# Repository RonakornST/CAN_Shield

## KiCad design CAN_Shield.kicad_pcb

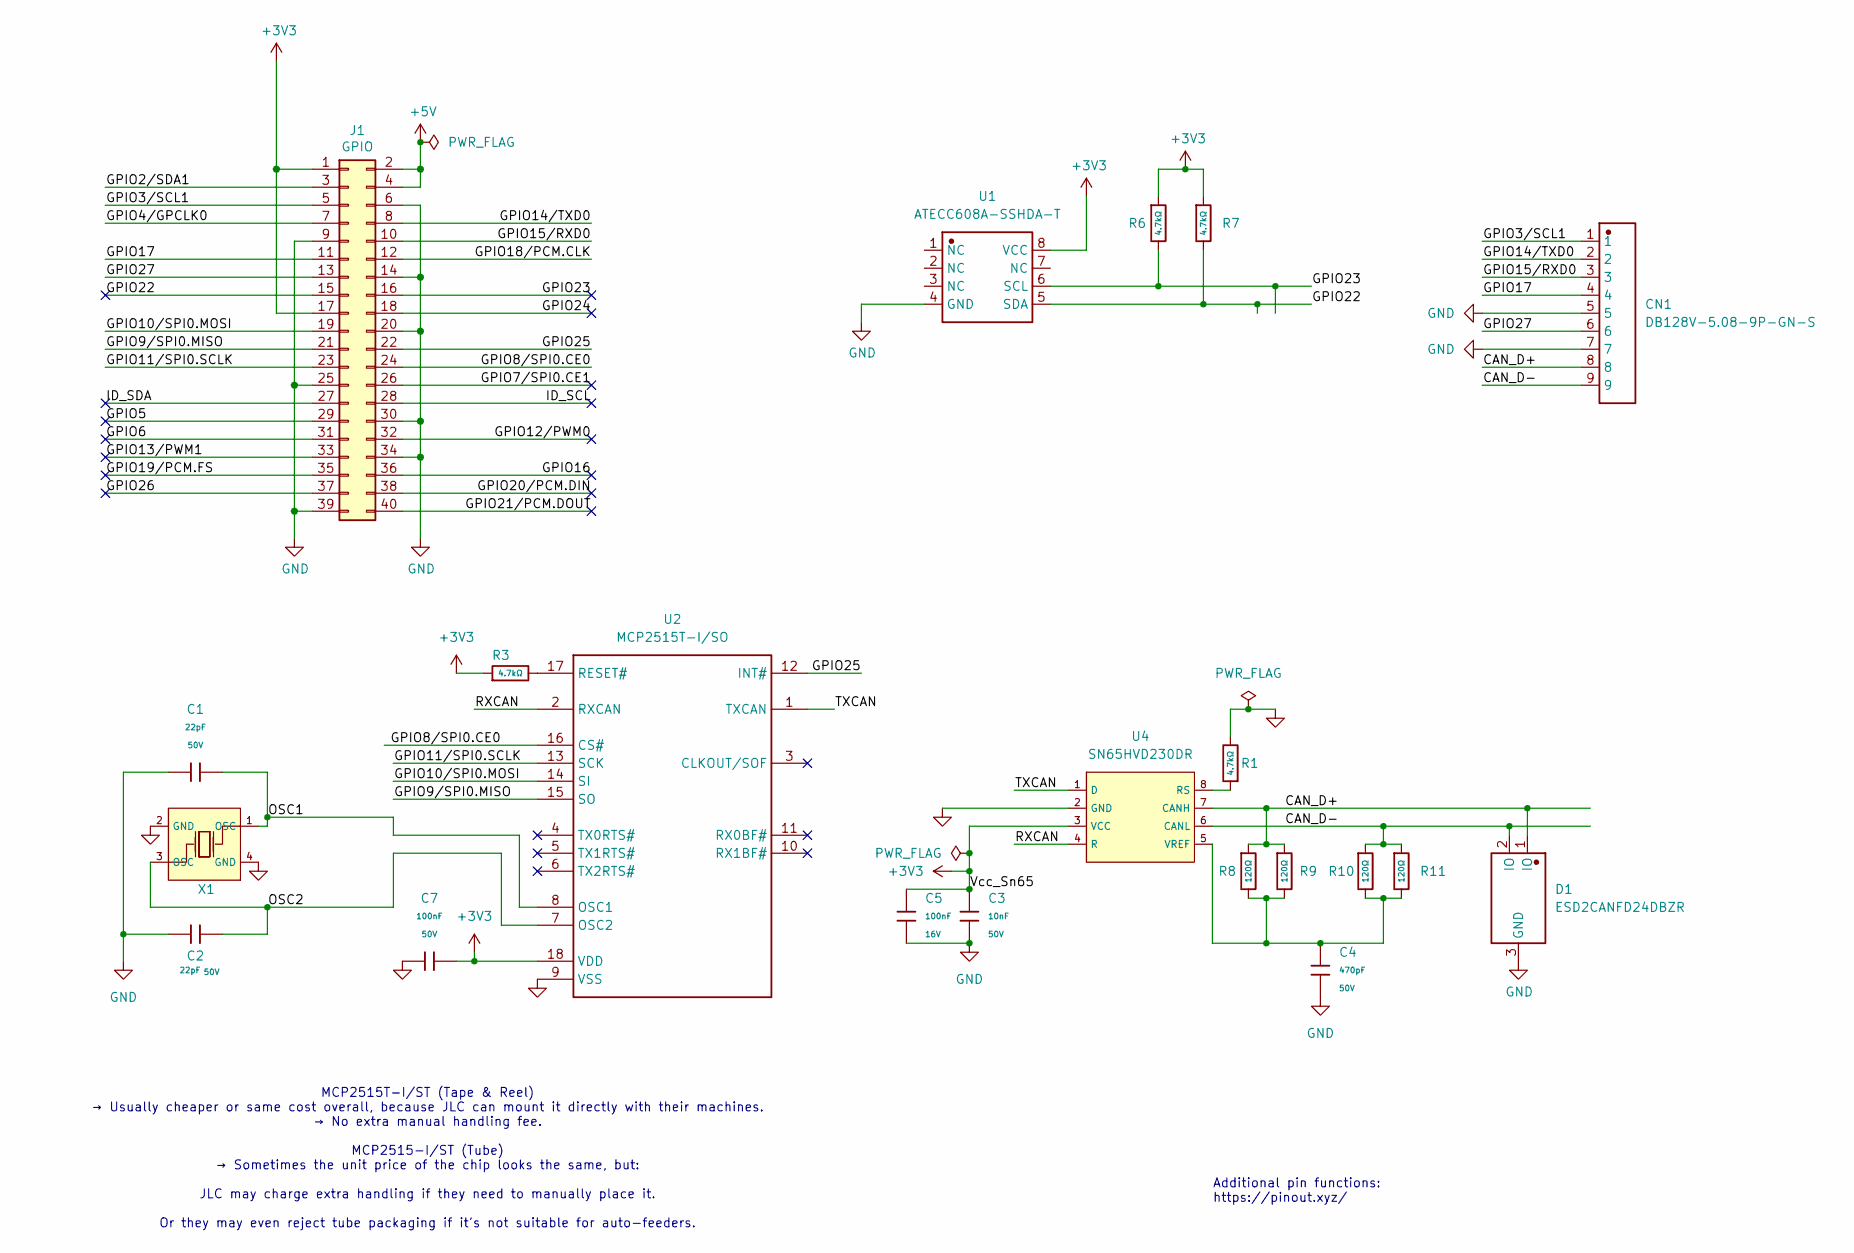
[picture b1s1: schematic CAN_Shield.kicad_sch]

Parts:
C1, C2: 22pF; C_0402; Voltage Rated 50V; Tolerance ±5%; Part 0402CG220J500NT; LCSC C1555
C3: 10nF; C_0402; Voltage Rated 50V; Tolerance ±10%; Part CL05B103KB5NNNC; LCSC C15195
C4: 470pF; C_0402; Voltage Rated 50V; Tolerance ±10%; Part 0402B471K500NT; LCSC C1537
C5: 100nF; C_0402; Voltage Rated 16V; Tolerance ±10%; Part CL05B104KO5NNNC; LCSC C1525
C7: 100nF; C_0603; Voltage Rated 50V; Tolerance ±10%; Part CC0603KRX7R9BB104; LCSC C14663
CN1: DB128V-5.08-9P-GN-S; CONN-TH_9P-P5.08_DIBO_DB128V-5.08-9P-GN-S; Manufacturer Part DB128V-5.08-9P-GN-S
D1: ESD2CANFD24DBZR; TI ESD2CANFD24DBZR; Manufacturer Part ESD2CANFD24DBZR
J1: GPIO; PinSocket_2x20_P2.54mm_Vertical
R1, R3, R6, R7: 4.7kΩ; R_0402; Overload Voltage (Max) 50V; Tolerance ±1%; Part 0402WGF4701TCE; LCSC C25900
R8, R9, R10, R11: 120Ω; R_0402; Overload Voltage (Max) 50V; Tolerance ±1%; Part 0402WGF1200TCE; LCSC C25079
U1: ATECC608A-SSHDA-T; MICROCHIP ATECC608A-SSHDA-T; Manufacturer Part ATECC608A-SSHDA-T
U2: MCP2515T-I/SO; MCP2515T-IST_SOIC-18_L11.6-W7.5-P1.27-LS10.3-BL; Manufacturer Part MCP2515T-I/SO
U4: SN65HVD230DR; SOIC-8_L4.9-W3.9-P1.27-LS6.0-BL; Supply Voltage 3V~3.6V; Part SN65HVD230DR; LCSC C12084
X1: X322516MLB4SI; OSC-SMD_4P-L3.2-W2.5-BL; Frequency Tolerance ±10ppm; Part X322516MLB4SI; LCSC C13738

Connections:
+3V3: C3.1, C5.1, C7.2, J1.1, J1.17, R3.1, R6.1, R7.1, U1.8 (VCC), U2.18 (VDD), U4.3 (VCC)
+5V: J1.2, J1.4
/CAN_D+: CN1.8, D1.1 (IO), R8.1, R9.1, U4.7 (CANH)
/CAN_D-: CN1.9, D1.2 (IO), R10.1, R11.1, U4.6 (CANL)
/GPIO2/SDA1: J1.3
/GPIO3/SCL1: CN1.1, J1.5
/GPIO4/GPCLK0: J1.7
/GPIO5: J1.29
/GPIO6: J1.31
/GPIO7/SPI0.CE1: J1.26
/GPIO8/SPI0.CE0: J1.24, U2.16 (CS#)
/GPIO9/SPI0.MISO: J1.21, U2.15 (SO)
/GPIO10/SPI0.MOSI: J1.19, U2.14 (SI)
/GPIO11/SPI0.SCLK: J1.23, U2.13 (SCK)
/GPIO12/PWM0: J1.32
/GPIO13/PWM1: J1.33
/GPIO14/TXD0: CN1.2, J1.8
/GPIO15/RXD0: CN1.3, J1.10
/GPIO16: J1.36
/GPIO17: CN1.4, J1.11
/GPIO18/PCM.CLK: J1.12
/GPIO19/PCM.FS: J1.35
/GPIO20/PCM.DIN: J1.38
/GPIO21/PCM.DOUT: J1.40
/GPIO22: J1.15, R7.2, U1.5 (SDA)
/GPIO23: J1.16, R6.2, U1.6 (SCL)
/GPIO24: J1.18
/GPIO25: J1.22, U2.12 (INT#)
/GPIO26: J1.37
/GPIO27: CN1.6, J1.13
/ID_SCL: J1.28
/ID_SDA: J1.27
/OSC1: C1.2, U2.8 (OSC1), X1.1 (OSC)
/OSC2: C2.2, U2.7 (OSC2), X1.3 (OSC)
/RXCAN: U2.2 (RXCAN), U4.4 (R)
/TXCAN: U2.1 (TXCAN), U4.1 (D)
GND: C1.1, C2.1, C3.2, C4.2, C5.2, C7.1, CN1.5, CN1.7, D1.3 (GND), J1.6, J1.9, J1.14, J1.20, J1.25, J1.30, J1.34, J1.39, R1.2, U1.4 (GND), U2.9 (VSS), U4.2 (GND), X1.2 (GND), X1.4 (GND)
unnamed: R3.2, U2.17 (RESET#)
unnamed: R1.1, U4.8 (RS)
unnamed: C4.1, R8.2, R9.2, R10.2, R11.2, U4.5 (VREF)

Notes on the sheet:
Additional pin functions: https://pinout.xyz/
MCP2515T-I/ST (Tape & Reel) → Usually cheaper or same cost overall, because JLC can mount it directly with their machines. → No extra manual handling fee. MCP2515-I/ST (Tube) → Sometimes the unit price of the chip looks the same, but: JLC may charge extra handling if they need to manually place it.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

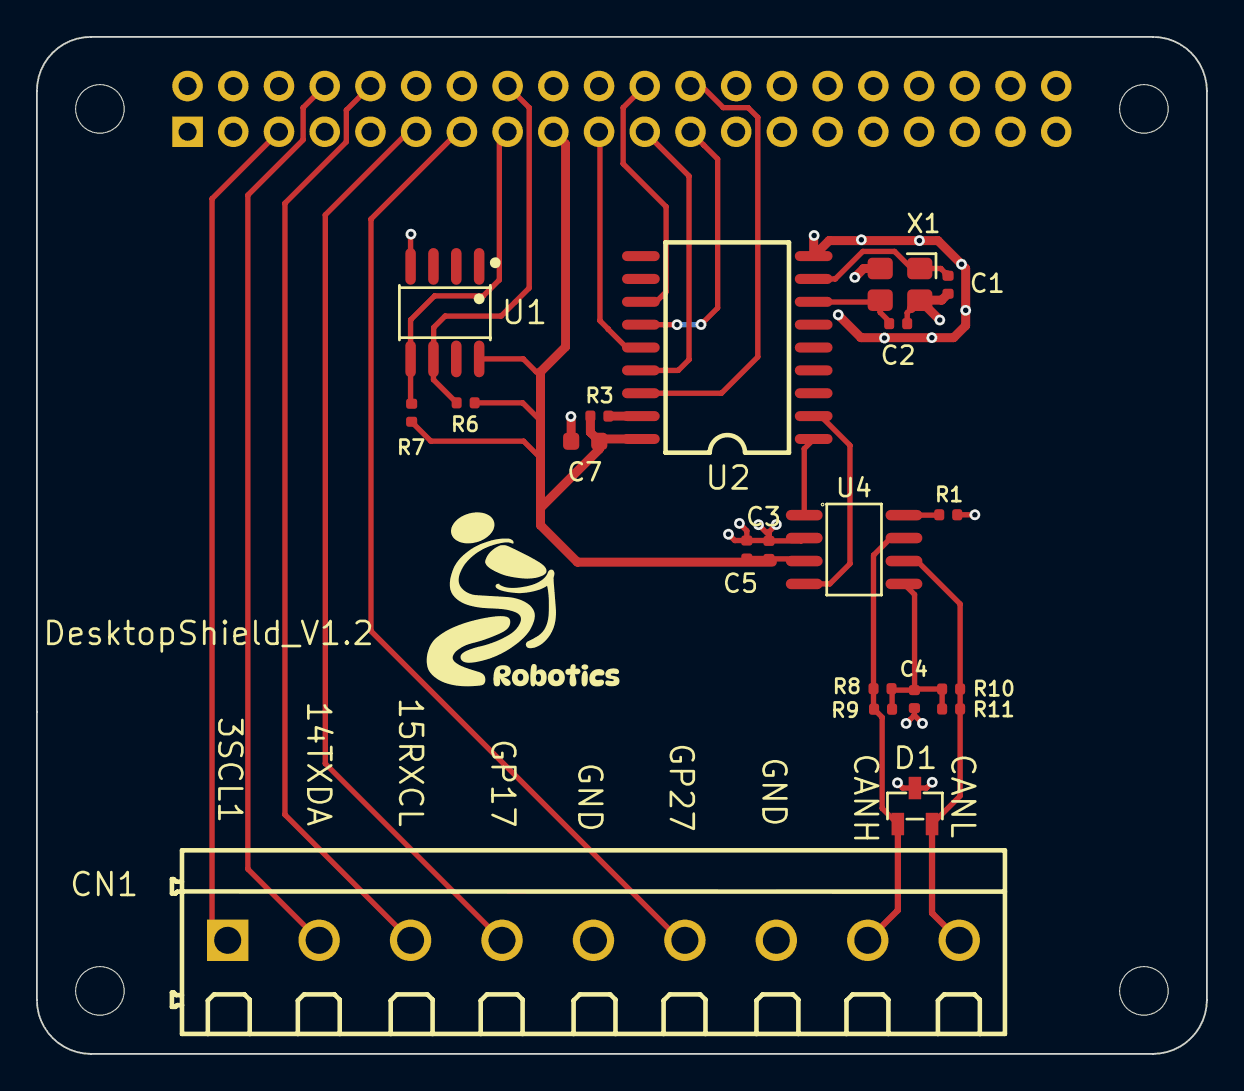
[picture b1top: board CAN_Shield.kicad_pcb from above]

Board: 2 copper layers, 65.0 x 56.5 mm, 25 parts (1 on the bottom side), 24 nets.

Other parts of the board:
MH1, MH2, MH3, MH4: MountingHole_2.7mm_M2.5

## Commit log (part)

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2025-09-22 Add .gitattributes and normalize line endings
2025-09-22 Add .gitattributes
2025-09-24 finished layout with 9 pin screw terminal, Unfinished edge extend and diff pair CAN
2025-09-24 add copper pour (forgot in last commit) and tranfer via for signal
2025-09-24 change from gpio to gnd at screw terminal and add copper pour for gnd
2025-09-24 add R and C to CAN H,L diff pair
2025-09-24 add silk screen for pin of screw terminal
2025-09-24 fix silkscreen overlapse by editing screw terminal footprint
2025-09-24 fix erc (thermal relief connection to zone incomplete (min spoke count 2 actual 1) by edit thermal relief gap from 0.5 to 0.3 mm
2025-09-24 fix warning about not enough clearance between gnd pour around gpio header
2025-09-25 remove transfer via and fix erc: logo silk screen
2025-09-25 extend pcb edge for smt header by double click the line and change from User.Drawing to Edgecuts
2025-09-26 change can diff pair trace width to 0.35 mm get 133ohm zdiff
2025-09-29 tune CAN diff pair skew
2026-04-29 quickly add 4 pin screw terminal block for I2C and move old SDA and SCL to new screw terminal block
2026-04-29 rearrange pin order on 10 pin terminal block and copper fill
2026-04-29 fix DRC SCL1 unconnected track
2026-04-29 fix switch SCL1 and SDA1 silk screen
2026-04-30 finished schematics and layout for 3 terminal block except CAN
2026-04-30 commit CAN_Shield-backups/CAN_Shield-2026-04-30_212813.zip
2026-05-02 fix atecc608 silkscreen on pad (both lib and pcb editor) and adjust TxRx can distance
2026-05-07 add more pin for right terminal block (unfinished import footprint and arrangement with unfinished schematics and layout)
2026-05-07 increase terminal block and 40 pin header spacing for easy soldering, also use DB-7P instead of 8 pin, add ESD diode for CAN
2026-05-10 finished can split termination and TVS diode layout
2026-05-11 add both bulk and bypass cap for sn65, increase spaing for crystal and add guard trace for crystal
2026-05-11 add logo and stiching via for guard trace
2026-05-11 recheck to add all change
2026-06-04 Create PCB step file but stll not add IC cad file
